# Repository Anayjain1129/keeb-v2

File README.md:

# Keeb

### Why did I make it?
I made it cause I have a freaking 60% keeb and I really need function keys also It has 2 RE which i can use for like brightness or volume stuff.

### What was the hardest part about this ?
It think everthing was cause it's like I love to learn new things so yea I love to make and learn new thing.

Features:

- 2x EC11 Rotary Encoder - For Volume, Brightness etc
- 74x keys
- Raspberry Pi Pico
- Customised layout
- QMK firmware
- Highway branded PCB and case

### Schematic

### PCB 

### Case
- Bottom

- Middle plate

- Top

### 3D view of all parts together 

### Stickers & Handcolor

-Paint

Also at the back part which i have craved some part it is because I'm gonna hand paint it to make it more attractive, I wasn't about to use Blender because I'm cyurrently on Arch and im facing issues. I hope my keeb gets approved now!
I got my sister who is artist so yea sh'e currntly out of station rn but she so many ideas, And like I got so many hackclub stickers so I will use them too.

I have more But I dont have phone rn so i can not take pictures 

I have more But I dont have phone rn so i can not take pictures 

## BOM

| Name                                                          | Qty | Final Price - INR (USD) | Link                                                                                                                        |
| ------------------------------------------------------------- | --- | ----------------------- | ----------------------------------------------------------------------------------------------------------                  |
| Gateron EF Grayish                                            | 80  | 1560 ($18.19)           | [here](https://neomacro.in/products/gateron-ef-grayish)                                                                     |
| Durock Smokey Screw-In Stabilizers V2 (4+1 w/ 6.25u spacebar) | 1   | 1590 ($18.58)           | [here](https://stackskb.com/store/durock-smokey-screw-in-stabilizers-v2/)                                                   |
| Cherry Profile PBT Keycaps                                    | 1   | 1300 ($15.15)           | [here](https://stackskb.com/store/veekos-gradient-keycaps-cherry-profile-135-keys)                                          |
| Diode 1N4148 Through - Hole                                   | 100 | 100 ($1.17)             | [here](https://amzn.in/d/j3eLvoh)                                                                                           |
| EC11 Rotary Encoder                                           | 2   | 178 ($2.08)             | [here](https://amzn.in/d/hVRxzij)                                                                                           |
| M3 x 20mm Bolt                                                | 15  | 149 ($1.73)             | [here](https://amzn.in/d/8GRQWAB)                                                                                           |
| M3 Nuts                                                       | 8   | 100 ($1.16)             | [here](https://amzn.in/d/7UQtsm8)                                                                                           |
| M3 x 5mm Heatset Insert                                       | 25  | 179 ($2.09)             | [here](https://amzn.in/d/ixybuAc)                                                                                           |
| PCB - (Black Color)                                           | 5   | 6683 ($77.78)           ||
| Raspberry Pi Pico                                             | 1   | 449 ($5.19)             | [here](http://amazon.in/Raspberry-Pi-Headers-Soldered-Micro/dp/B08WPNM7JB/ref=sr_1_2?sr=8-2)                                |
| Top Case                                                      | 1   | Print Legion            |
| Bottom Case                                                   | 1   | Print Legion            |
| Middle Plate                                                  | 1   | Print Legion            |

## Total Pricing
The total price comes out to be 11,956.35 INR ($139.31) I'm not including the cost of case cause I will get it printed from Print Legion.

The pricing might slightly vary due to flash sales, and dollar market trends.

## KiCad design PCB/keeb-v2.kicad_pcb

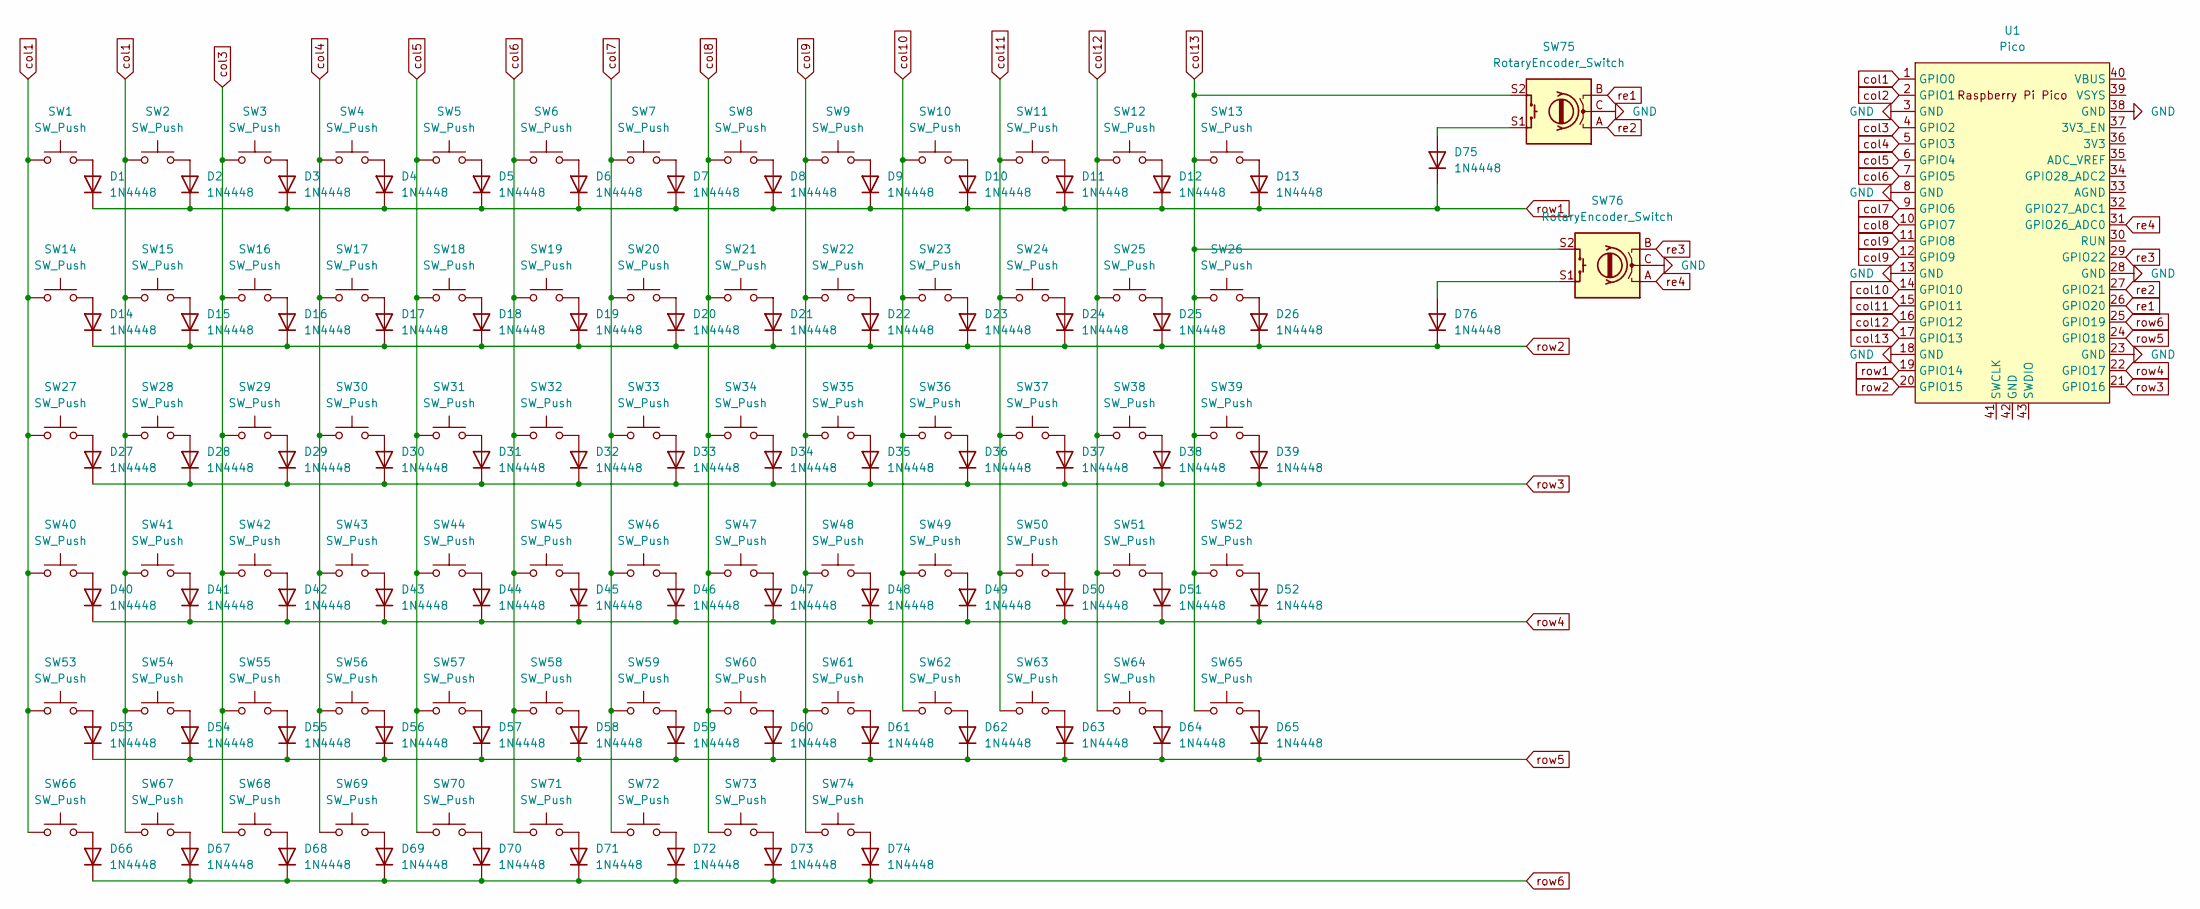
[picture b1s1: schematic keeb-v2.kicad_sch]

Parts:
D1, D2, D3, D4, D5, D6, D7, D8, D9, D10, D11, D12, D13, D14, D15, D16, D17, D18, D19, D20, D21, D22, D23, D24, D25, D26, D27, D28, D29, D30, D31, D32, D33, D34, D35, D36, D37, D38, D39, D40, D41, D42, D43, D44, D45, D46, D47, D48, D49, D50, D51, D52, D53, D54, D55, D56, D57, D58, D59, D60, D61, D62, D63, D64, D65, D66, D67, D68, D69, D70, D71, D72, D73, D74, D75, D76: 1N4448; D_DO-35_SOD27_P7.62mm_Horizontal
SW1, SW2, SW3, SW4, SW5, SW6, SW7, SW8, SW9, SW10, SW11, SW12, SW13, SW14, SW15, SW16, SW17, SW18, SW19, SW20, SW21, SW22, SW23, SW24, SW25, SW26, SW29, SW30, SW31, SW32, SW33, SW34, SW35, SW36, SW37, SW38, SW39, SW40, SW43, SW44, SW45, SW46, SW47, SW48, SW49, SW50, SW51, SW52, SW53, SW56, SW57, SW58, SW59, SW60, SW61, SW62, SW63, SW64, SW65: SW_Push; SW_Cherry_MX_1.00u_PCB
SW27: SW_Push; SW_Cherry_MX_2.00u_PCB
SW28, SW41: SW_Push; SW_Cherry_MX_1.50u_PCB
SW42: SW_Push; SW_Cherry_MX_1.75u_PCB
SW54, SW55: SW_Push; SW_Cherry_MX_2.25u_PCB
SW66: SW_Push; SW_Cherry_MX_2.75u_PCB
SW67, SW68, SW69, SW71, SW72, SW73, SW74: SW_Push; SW_Cherry_MX_1.25u_PCB
SW70: SW_Push; SW_Cherry_MX_6.25u_PCB
SW75, SW76: RotaryEncoder_Switch; RotaryEncoder_Alps_EC11E-Switch_Vertical_H20mm_CircularMoun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
U1: Pico; RPi_Pico_SMD_TH

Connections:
GND: SW75.C, SW76.C, U1.3 (GND), U1.8 (GND), U1.13 (GND), U1.18 (GND), U1.23 (GND), U1.28 (GND), U1.38 (GND)
unnamed: D1.2 (A), SW1.2
unnamed: D2.2 (A), SW2.2
unnamed: D3.2 (A), SW3.2
unnamed: D4.2 (A), SW4.2
unnamed: D5.2 (A), SW5.2
unnamed: D6.2 (A), SW6.2
unnamed: D7.2 (A), SW7.2
unnamed: D8.2 (A), SW8.2
unnamed: D9.2 (A), SW9.2
unnamed: D10.2 (A), SW10.2
unnamed: D11.2 (A), SW11.2
unnamed: D12.2 (A), SW12.2
unnamed: D13.2 (A), SW13.2
unnamed: D14.2 (A), SW14.2
unnamed: D15.2 (A), SW15.2
unnamed: D16.2 (A), SW16.2
unnamed: D17.2 (A), SW17.2
unnamed: D18.2 (A), SW18.2
unnamed: D19.2 (A), SW19.2
unnamed: D20.2 (A), SW20.2
unnamed: D21.2 (A), SW21.2
unnamed: D22.2 (A), SW22.2
unnamed: D23.2 (A), SW23.2
unnamed: D24.2 (A), SW24.2
unnamed: D25.2 (A), SW25.2
unnamed: D26.2 (A), SW26.2
unnamed: D27.2 (A), SW27.2
unnamed: D28.2 (A), SW28.2
unnamed: D29.2 (A), SW29.2
unnamed: D30.2 (A), SW30.2
unnamed: D31.2 (A), SW31.2
unnamed: D32.2 (A), SW32.2
unnamed: D33.2 (A), SW33.2
unnamed: D34.2 (A), SW34.2
unnamed: D35.2 (A), SW35.2
unnamed: D36.2 (A), SW36.2
unnamed: D37.2 (A), SW37.2
unnamed: D38.2 (A), SW38.2
unnamed: D39.2 (A), SW39.2
unnamed: D40.2 (A), SW40.2
unnamed: D41.2 (A), SW41.2
unnamed: D42.2 (A), SW42.2
unnamed: D43.2 (A), SW43.2
unnamed: D44.2 (A), SW44.2
unnamed: D45.2 (A), SW45.2
unnamed: D46.2 (A), SW46.2
unnamed: D47.2 (A), SW47.2
unnamed: D48.2 (A), SW48.2
unnamed: D49.2 (A), SW49.2
unnamed: D50.2 (A), SW50.2
unnamed: D51.2 (A), SW51.2
unnamed: D52.2 (A), SW52.2
unnamed: D53.2 (A), SW53.2
unnamed: D54.2 (A), SW54.2
unnamed: D55.2 (A), SW55.2
unnamed: D56.2 (A), SW56.2
unnamed: D57.2 (A), SW57.2
unnamed: D58.2 (A), SW58.2
unnamed: D59.2 (A), SW59.2
unnamed: D60.2 (A), SW60.2
unnamed: D61.2 (A), SW61.2
unnamed: D62.2 (A), SW62.2
unnamed: D63.2 (A), SW63.2
unnamed: D64.2 (A), SW64.2
unnamed: D65.2 (A), SW65.2
unnamed: D66.2 (A), SW66.2
unnamed: D67.2 (A), SW67.2
unnamed: D68.2 (A), SW68.2
unnamed: D69.2 (A), SW69.2
unnamed: D70.2 (A), SW70.2
unnamed: D71.2 (A), SW71.2
unnamed: D72.2 (A), SW72.2
unnamed: D73.2 (A), SW73.2
unnamed: D74.2 (A), SW74.2
unnamed: D75.2 (A), SW75.S1
unnamed: D76.2 (A), SW76.S1
col1: SW1.1, SW2.1, SW14.1, SW15.1, SW27.1, SW28.1, SW40.1, SW41.1, SW53.1, SW54.1, SW66.1, SW67.1, U1.1 (GPIO0)
col2: U1.2 (GPIO1)
col3: SW3.1, SW16.1, SW29.1, SW42.1, SW55.1, SW68.1, U1.4 (GPIO2)
col4: SW4.1, SW17.1, SW30.1, SW43.1, SW56.1, SW69.1, U1.5 (GPIO3)
col5: SW5.1, SW18.1, SW31.1, SW44.1, SW57.1, SW70.1, U1.6 (GPIO4)
col6: SW6.1, SW19.1, SW32.1, SW45.1, SW58.1, SW71.1, U1.7 (GPIO5)
col7: SW7.1, SW20.1, SW33.1, SW46.1, SW59.1, SW72.1, U1.9 (GPIO6)
col8: SW8.1, SW21.1, SW34.1, SW47.1, SW60.1, SW73.1, U1.10 (GPIO7)
col9: SW9.1, SW22.1, SW35.1, SW48.1, SW61.1, SW74.1, U1.11 (GPIO8), U1.12 (GPIO9)
col10: SW10.1, SW23.1, SW36.1, SW49.1, SW62.1, U1.14 (GPIO10)
col11: SW11.1, SW24.1, SW37.1, SW50.1, SW63.1, U1.15 (GPIO11)
col12: SW12.1, SW25.1, SW38.1, SW51.1, SW64.1, U1.16 (GPIO12)
col13: SW13.1, SW26.1, SW39.1, SW52.1, SW65.1, SW75.S2, SW76.S2, U1.17 (GPIO13)
re1: SW75.B, U1.26 (GPIO20)
re2: SW75.A, U1.27 (GPIO21)
re3: SW76.B, U1.29 (GPIO22)
re4: SW76.A, U1.31 (GPIO26_ADC0)
row1: D1.1 (K), D2.1 (K), D3.1 (K), D4.1 (K), D5.1 (K), D6.1 (K), D7.1 (K), D8.1 (K), D9.1 (K), D10.1 (K), D11.1 (K), D12.1 (K), D13.1 (K), D75.1 (K), U1.19 (GPIO14)
row2: D14.1 (K), D15.1 (K), D16.1 (K), D17.1 (K), D18.1 (K), D19.1 (K), D20.1 (K), D21.1 (K), D22.1 (K), D23.1 (K), D24.1 (K), D25.1 (K), D26.1 (K), D76.1 (K), U1.20 (GPIO15)
row3: D27.1 (K), D28.1 (K), D29.1 (K), D30.1 (K), D31.1 (K), D32.1 (K), D33.1 (K), D34.1 (K), D35.1 (K), D36.1 (K), D37.1 (K), D38.1 (K), D39.1 (K), U1.21 (GPIO16)
row4: D40.1 (K), D41.1 (K), D42.1 (K), D43.1 (K), D44.1 (K), D45.1 (K), D46.1 (K), D47.1 (K), D48.1 (K), D49.1 (K), D50.1 (K), D51.1 (K), D52.1 (K), U1.22 (GPIO17)
row5: D53.1 (K), D54.1 (K), D55.1 (K), D56.1 (K), D57.1 (K), D58.1 (K), D59.1 (K), D60.1 (K), D61.1 (K), D62.1 (K), D63.1 (K), D64.1 (K), D65.1 (K), U1.24 (GPIO18)
row6: D66.1 (K), D67.1 (K), D68.1 (K), D69.1 (K), D70.1 (K), D71.1 (K), D72.1 (K), D73.1 (K), D74.1 (K), U1.25 (GPIO19)

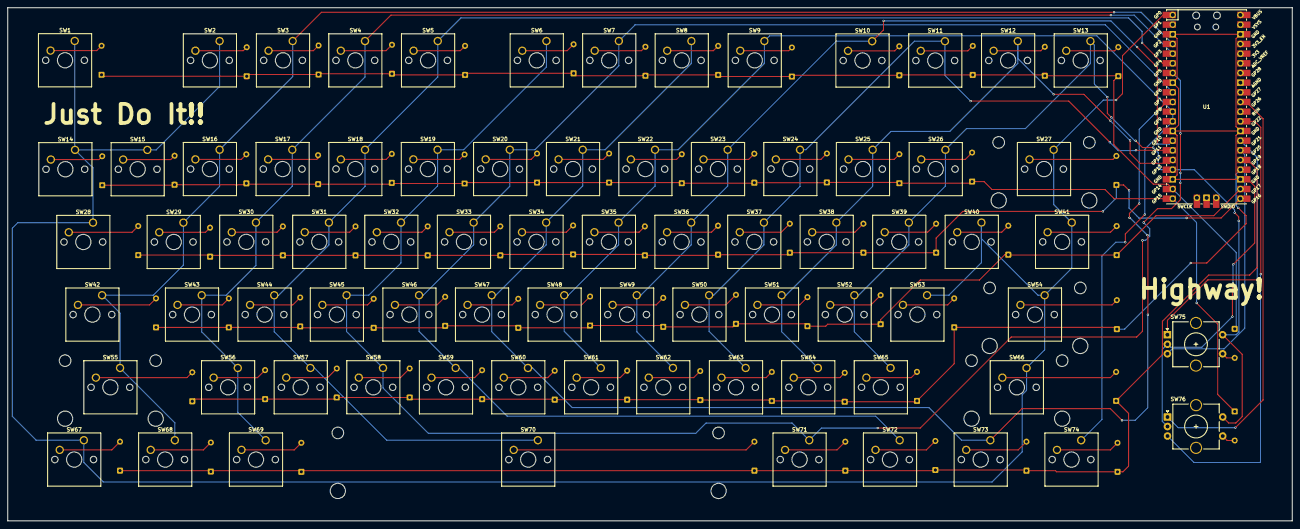
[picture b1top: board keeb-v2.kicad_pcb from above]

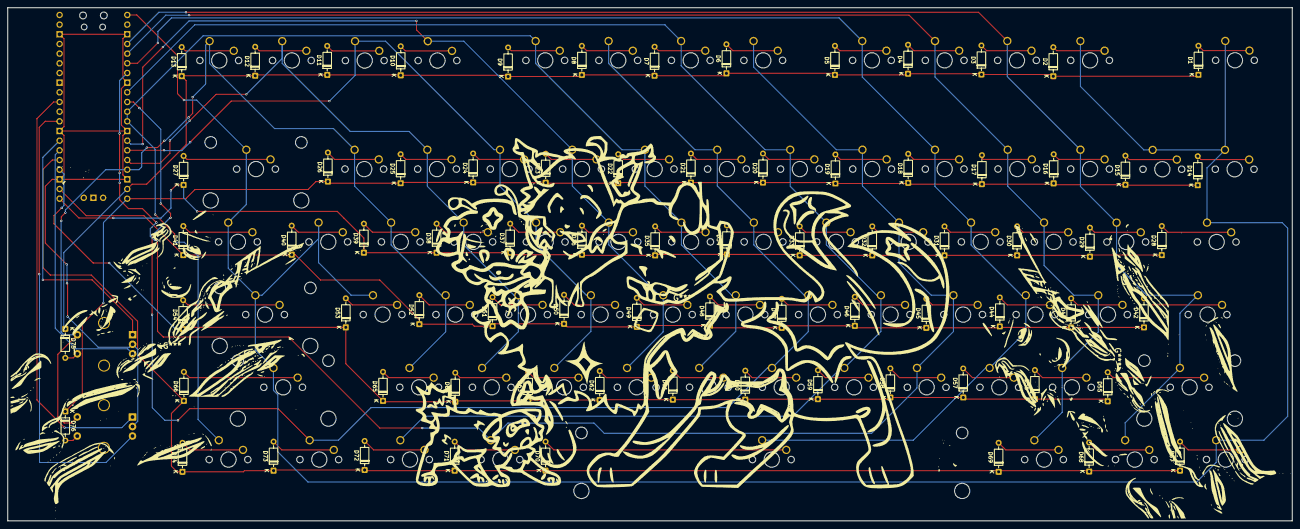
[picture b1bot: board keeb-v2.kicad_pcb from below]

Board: 2 copper layers, 337.4 x 134.8 mm, 153 parts (76 on the bottom side), 99 nets.

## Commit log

2025-06-30 Create null
2025-07-12 Create nill
2025-07-18 Rename bom (1).csv to bom.csv
